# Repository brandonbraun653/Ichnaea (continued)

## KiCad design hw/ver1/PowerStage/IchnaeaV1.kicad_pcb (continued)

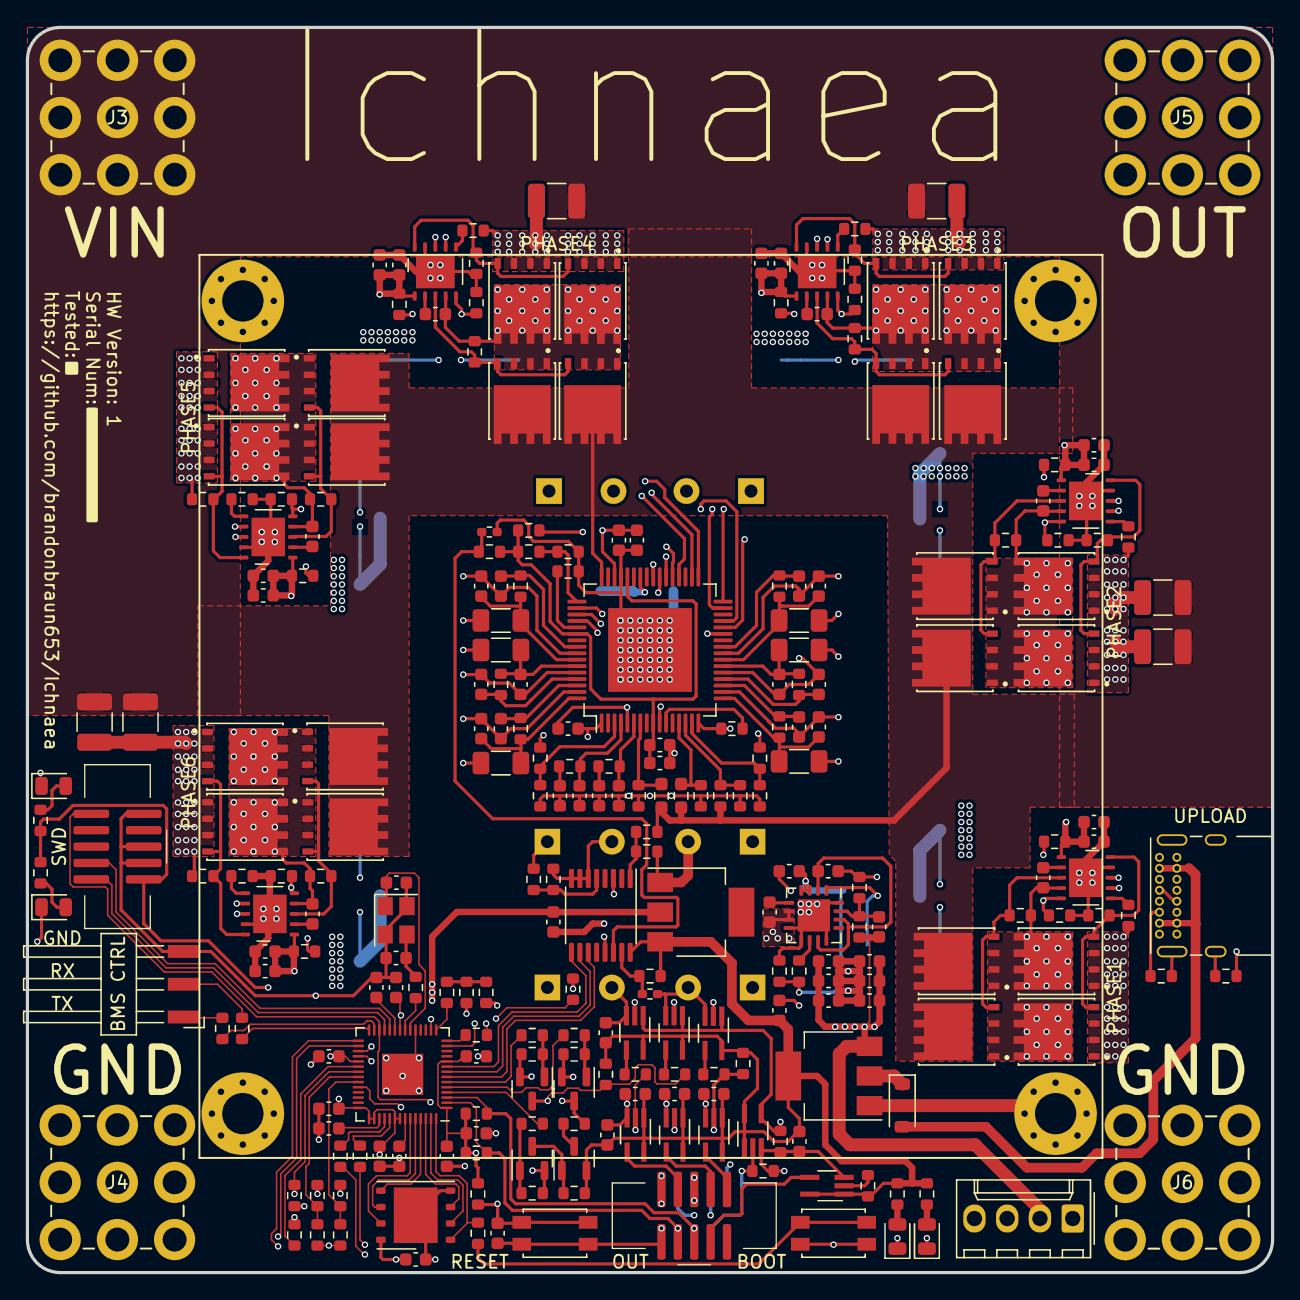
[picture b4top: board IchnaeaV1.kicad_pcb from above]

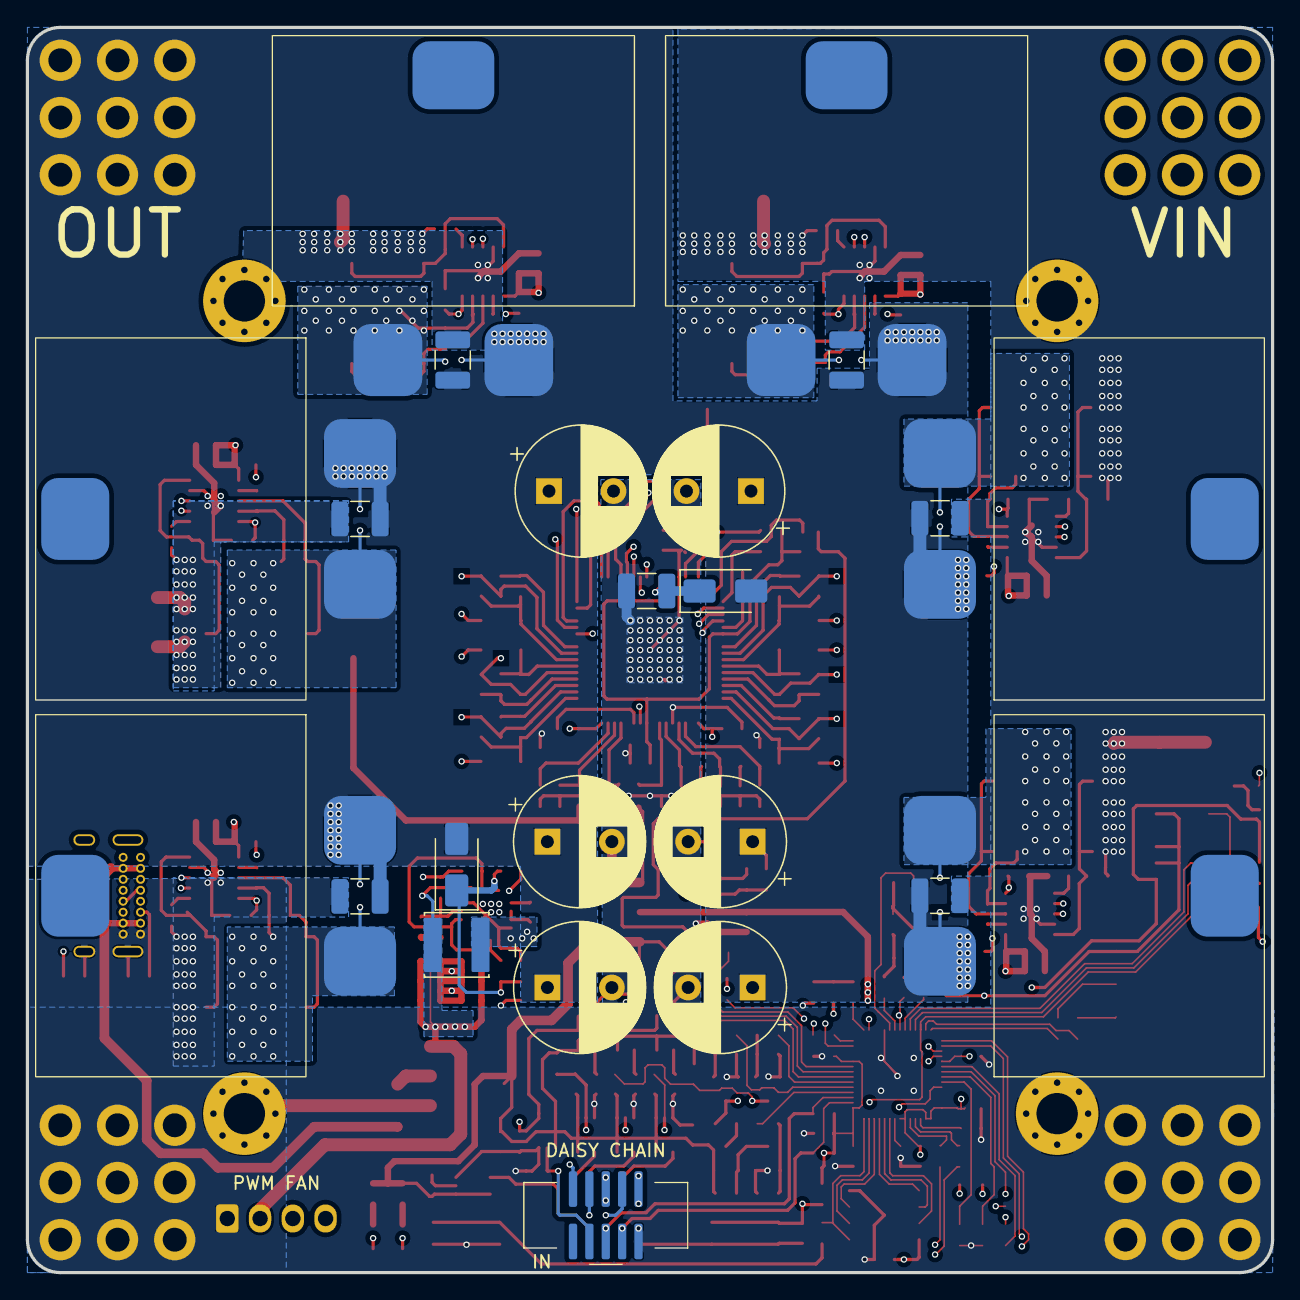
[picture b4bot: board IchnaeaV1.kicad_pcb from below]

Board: 4 copper layers, 96.5 x 96.5 mm, 283 parts (23 on the bottom side), 165 nets.

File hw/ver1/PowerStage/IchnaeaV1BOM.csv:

Reference,Value,Digikey,LCSC,Footprint,Datasheet,Qty,DNP
"R1,R55,R60,R65,R70,R75,R102,R103,R104,R110,R112",0,N/A,C21189,Resistor_SMD:R_0603_1608Metric,~,11,
"C71,C79",15pF,N/A,C1644,Capacitor_SMD:C_0603_1608Metric,~,2,
"C12,C13,C77",47pF,N/A,C1671,Capacitor_SMD:C_0603_1608Metric,~,3,
"C2,C4,C8,C10,C11,C14,C15,C29,C31,C35,C37,C41,C43,C47,C49,C53,C55,C60,C61,C65,C66,C67,C68,C70,C72,C82,C83,C84,C86,C87,C88,C90,C91,C92,C93",100nF,N/A,C14663,Capacitor_SMD:C_0603_1608Metric,~,35,
"C3,C5,C30,C32,C36,C38,C42,C44,C48,C50,C54,C56",470nF,N/A,C1623,Capacitor_SMD:C_0603_1608Metric,~,12,
"C1,C18,C21,C28,C34,C40,C46,C52,C78,C80,C81,C89",4.7uF,N/A,C19666,Capacitor_SMD:C_0603_1608Metric,~,12,
"L1,L2,L3,L4,L5,L6",4.7uH,PQ2614BLA-3R3K-ND,N/A,Inductors:Bournes_L_PQ2614BLA,~,6,
"C7,C9,C69,C73,C74,C75,C76",10uF,N/A,C96446,Capacitor_SMD:C_0603_1608Metric,~,7,
L7,22uH,240-2706-1-ND,N/A,Inductors:TYS5020220M,~,1,
"C22,C25,C26,C27,C62,C63",220uF,1189-3789-1-ND,N/A,Capacitor_THT:CP_Radial_D10.0mm_P5.00mm,~,6,
"R24,R26",22,N/A,C23345,Resistor_SMD:R_0603_1608Metric,~,2,
"R11,R19,R49,R50",100,N/A,C22775,Resistor_SMD:R_0603_1608Metric,~,4,
"R9,R10,R131,R132",510,N/A,C23193,Resistor_SMD:R_0603_1608Metric,~,4,
"R6,R32,R107,R117,R118,R119,R121,R128",1k,N/A,C21190,Resistor_SMD:R_0603_1608Metric,~,8,
"R8,R120,R129",2k,N/A,C22975,Resistor_SMD:R_0603_1608Metric,~,3,
R31,3k,N/A,C4211,Resistor_SMD:R_0603_1608Metric,~,1,
"R93,R94",4.7k,N/A,C23162,Resistor_SMD:R_0603_1608Metric,~,2,
"R108,R109",5.1k,N/A,C23186,Resistor_SMD:R_0603_1608Metric,~,2,
"R5,R59,R64,R69,R74,R79",6.2k,N/A,C4260,Resistor_SMD:R_0603_1608Metric,~,6,
R98,7.5k,N/A,C23234,Resistor_SMD:R_0603_1608Metric,~,1,
"R2,R3,R12,R13,R16,R21,R23,R28,R30,R33,R35,R44,R45,R46,R48,R51,R52,R53,R54,R56,R57,R61,R62,R66,R67,R71,R72,R76,R77,R80,R81,R82,R83,R84,R85,R86,R87,R88,R89,R90,R91,R92,R95,R96,R97",10k,N/A,C25804,Resistor_SMD:R_0603_1608Metric,~,45,
"TH1,TH2",10k-NTC,445-2550-1-ND,N/A,Resistor_SMD:R_0402_1005Metric_Pad0.72x0.64mm_HandSolder,~,2,
"R18,R39",15k,N/A,C22809,Resistor_SMD:R_0603_1608Metric,~,2,
R7,22k,N/A,C31850,Resistor_SMD:R_0603_1608Metric,~,1,
R15,27k,N/A,C22967,Resistor_SMD:R_0603_1608Metric,~,1,
R36,30k,N/A,C22984,Resistor_SMD:R_0603_1608Metric,~,1,
"R27,R100",68k,N/A,C23231,Resistor_SMD:R_0603_1608Metric,~,2,
R29,100k,N/A,C25803,Resistor_SMD:R_0603_1608Metric,~,1,
R42,120k,N/A,C25808,Resistor_SMD:R_0603_1608Metric,~,1,
"R14,R17,R22,R43",470k,N/A,C23178,Resistor_SMD:R_0603_1608Metric,~,4,
R99,510k,N/A,C23192,Resistor_SMD:R_0603_1608Metric,~,1,
"R41,R47",787k,P787KHCT-ND,N/A,Resistor_SMD:R_0603_1608Metric_Pad0.98x0.95mm_HandSolder,~,2,
Y1,12MHz,XC2613CT-ND,N/A,Crystal:Crystal_SMD_3225-4Pin_3.2x2.5mm,~,1,
"C6,C33,C39,C45,C51,C57,C64",10uF-75V,445-CGA6P1X7R1N106M250ACCT-ND,,Capacitor_SMD:C_1210_3225Metric_Pad1.33x2.70mm_HandSolder,~,7,
"C19,C20,C23,C24,C58,C59",10uF-100V,490-16266-1-ND,,Capacitor_SMD:C_1210_3225Metric_Pad1.33x2.70mm_HandSolder,~,6,
"R4,R58,R63,R68,R73,R78",6.2k-0.25w,311-6.20KFRCT-ND,N/A,Resistor_SMD:R_1206_3216Metric_Pad1.30x1.75mm_HandSolder,~,6,
"U11,U12,U13,U14,U15,U16,U17,U18",74AHC1G126,74AHCT1G126SE-7DICT-ND,N/A,Package_TO_SOT_SMD:SOT-353_SC-70-5_Handsoldering,http://www.ti.com/lit/sg/scyt129e/scyt129e.pdf,8,
U2,74HC4051PW,1727-3064-1-ND,N/A,Package_SO:TSSOP-16_4.4x5mm_P0.65mm,http://www.ti.com/lit/ds/symlink/cd74hc4051.pdf,1,
U19,AP66200FVBW-13,31-AP66200FVBW-13CT-ND,N/A,Package_DFN_QFN:QFN-16-1EP_4x4mm_P0.65mm_EP2.5x2.5mm,https://www.diodes.com/assets/Datasheets/AP66200.pdf,1,
D4,B5819W,N/A,C8598,Diode_SMD:D_SOD-123,~,1,
J11,BMS_Serial,952-3232-ND,N/A,Connector_Harwin:Harwin_M20-89003xx_1x03_P2.54mm_Horizontal,~,1,
SW3,Boot,P11081SCT-ND,N/A,Button_Switch_SMD:SW_SPST_EVQP2,~,1,
Q5,BSS84,5272-BSS84CT-ND,N/A,Package_TO_SOT_SMD:SOT-23,http://assets.nexperia.com/documents/data-sheet/BSS84.pdf,1,
"Q3,Q4,Q6",BSS138,5272-BSS138CT-ND,N/A,Package_TO_SOT_SMD:SOT-23,https://www.onsemi.com/pub/Collateral/BSS138-D.PDF,3,
J1,DaisyChain-In,1175-1629-ND,N/A,Connectors:JTAG_2x05_P1_27mm_Shrouded_SMD,~,1,
J9,DaisyChain-Out,1175-1629-ND,N/A,Connectors:JTAG_2x05_P1_27mm_Shrouded_SMD,~,1,
J8,FanConnector,WM4330-ND,N/A,Connector_Molex:Molex_KK-254_AE-6410-04A_1x04_P2.54mm_Vertical,~,1,
"D2,D7",Green LED,N/A,C2297,LED_SMD:LED_0805_2012Metric,~,2,
"U1,U5,U6,U7,U8,U9",HIP2210,20-HIP2210FRTZ-TCT-ND,N/A,DFN:TDFN-10-1EP_4x4mm_P0.8mm_EP2.6x3mm,https://www.renesas.com/us/en/document/dst/hip2210-hip2211-d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,6,
U4,LM1117MP-3.3,N/A,C6186,Package_TO_SOT_SMD:SOT-223-3_TabPin2,http://www.ti.com/lit/ds/symlink/lm1117.pdf,1,
U21,LM1117MP-5.0,N/A,C6187,Package_TO_SOT_SMD:SOT-223-3_TabPin2,http://www.ti.com/lit/ds/symlink/lm1117.pdf,1,
U3,LTC7871,505-LTC7871ELWE#PBF-ND,C690288,Package_QFP:LQFP-64-1EP_10x10mm_P0.5mm_EP6.5x6.5mm,https://www.analog.com/media/en/technical-documentation/data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,1,
"Q1,Q2,Q7,Q8,Q9,Q10,Q11,Q12,Q13,Q14,Q15,Q16,Q17,Q18,Q19,Q20,Q21,Q22,Q23,Q24,Q25,Q26,Q27,Q28",MCAC80N10Y,353-MCAC80N10Y-TPCT-ND,N/A,Mosfets:TRANS_BSC076N06NS3-G,https://www.mccsemi.com/pdf/Products/MCAC80N10Y(DFN5060).pdf,24,
SW4,Reset,P11081SCT-ND,N/A,Button_Switch_SMD:SW_SPST_EVQP2,~,1,
U10,RP2040,2648-SC0914(13)CT-ND,C2040,Package_DFN_QFN:QFN-56-1EP_7x7mm_P0.4mm_EP3.2x3.2mm,https://datasheets.raspberrypi.com/rp2040/rp2040-datasheet.pdf,1,
"J3,J4,J5,J6",Screw_Terminal_01x09,732-74651195RCT-ND,N/A,Connectors:CONN_74651195R_WRE,~,4,
"D1,D3",SS210,N/A,C14996,Diode_SMD:D_SMA,~,2,
P1,USB_C_Plug_USB2.0,2073-USB4085-GF-ACT-ND,N/A,Connector_USB:USB_C_Receptacle_GCT_USB4085,https://www.usb.org/sites/default/files/documents/usb_type-c.zip,1,
U20,W25Q32JVZP,W25Q32JVZPIQ-ND,N/A,Package_SON:WSON-8-1EP_6x5mm_P1.27mm_EP3.4x4.3mm,http://www.winbond.com/resource-files/w25q32jv%20revg%200327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,1,
"D5,D6",Yellow LED,N/A,C2296,LED_SMD:LED_0805_2012Metric,~,2,
J2,~,1175-1629-ND,,Connectors:JTAG_2x05_P1_27mm_Shrouded_SMD,~,1,

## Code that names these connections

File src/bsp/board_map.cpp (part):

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      s_board_map.gpio[ GPIO_LTC_ADCSEL0 ].pin     = BSPV1::GPIO::PIN_OUT_ADC_SEL_0;
      s_board_map.gpio[ GPIO_LTC_ADCSEL1 ].pin     = BSPV1::GPIO::PIN_OUT_ADC_SEL_1;
      s_board_map.gpio[ GPIO_LTC_ADCSEL2 ].pin     = BSPV1::GPIO::PIN_OUT_ADC_SEL_2;
      s_board_map.gpio[ GPIO_LTC_CCM ].pin         = BSPV1::GPIO::PIN_OUT_LTC_CCM;
      s_board_map.gpio[ GPIO_LTC_DCM ].pin         = BSPV1::GPIO::PIN_OUT_LTC_DCM;
      s_board_map.gpio[ GPIO_LTC_RUN ].pin         = BSPV1::GPIO::PIN_IO_LTC_RUN;
      s_board_map.gpio[ GPIO_SPI_CS_LTC ].pin      = BSPV1::SPI::PIN_CS_0;
      s_board_map.pwm[ PWM_FAN_CONTROL ].pin       = BSPV1::PWM::PIN_OUT_FAN_CTL;
      s_board_map.pwm[ PWM_FAN_SENSE ].pin         = BSPV1::PWM::PIN_IN_FAN_SENSE;
      s_board_map.pwm[ PWM_LED_STATUS_0 ].pin      = BSPV1::GPIO::PIN_OUT_LED_STATUS_0;
      s_board_map.pwm[ PWM_LED_STATUS_1 ].pin      = BSPV1::GPIO::PIN_OUT_LED_STATUS_1;
      s_board_map.pwm[ PWM_LED_STATUS_2 ].pin      = BSPV1::GPIO::PIN_OUT_LED_STATUS_2;
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      s_board_map.ltc_num_phases                   = 6;
      s_board_map.ltc_setcur_rfb                   = 22'000.0f;
      s_board_map.adc[ ADC_MUTLIPLEXED_SENSE ].pin = BSPV2::ADC::PIN_MULTIPLEX;
      s_board_map.adc[ ADC_BOARD_REV ].pin         = BSPV2::ADC::PIN_BOARD_REV;
      s_board_map.adc[ ADC_IMON_BATT ].pin         = BSPV2::ADC::PIN_IMON_BATT;
      s_board_map.adc[ ADC_IMON_FLTR ].pin         = BSPV2::ADC::PIN_IMON_FLTR;
      s_board_map.gpio[ GPIO_LTC_ADCSEL0 ].pin     = BSPV2::GPIO::PIN_OUT_ADC_SEL_0;
      s_board_map.gpio[ GPIO_LTC_ADCSEL1 ].pin     = BSPV2::GPIO::PIN_OUT_ADC_SEL_1;
      s_board_map.gpio[ GPIO_LTC_ADCSEL2 ].pin     = BSPV2::GPIO::PIN_OUT_ADC_SEL_2;
      s_board_map.gpio[ GPIO_LTC_CCM ].pin         = BSPV2::GPIO::PIN_OUT_LTC_CCM;
      s_board_map.gpio[ GPIO_LTC_DCM ].pin         = BSPV2::GPIO::PIN_OUT_LTC_DCM;
      s_board_map.gpio[ GPIO_LTC_RUN ].pin         = BSPV2::GPIO::PIN_OUT_LTC_RUN;
      s_board_map.gpio[ GPIO_LTC_PWMEN ].pin       = BSPV2::GPIO::PIN_OUT_LTC_PWMEN;
      s_board_map.gpio[ GPIO_SPI_CS_LTC ].pin      = BSPV2::SPI::PIN_LTC_CS_0;
      s_board_map.gpio[ GPIO_SPI_CS_NOR ].pin      = BSPV2::SPI::PIN_NOR_CS_0;
      s_board_map.pwm[ PWM_FAN_CONTROL ].pin       = BSPV2::PWM::PIN_OUT_FAN_CTL;
      s_board_map.pwm[ PWM_FAN_SENSE ].pin         = BSPV2::PWM::PIN_IN_FAN_SENSE;
      s_board_map.pwm[ PWM_LED_STATUS_0 ].pin      = BSPV2::PWM::PIN_OUT_LED_STATUS_0;
      s_board_map.pwm[ PWM_LED_STATUS_1 ].pin      = BSPV2::PWM::PIN_OUT_LED_STATUS_1;
      s_board_map.pwm[ PWM_LED_STATUS_2 ].pin      = BSPV2::PWM::PIN_OUT_LED_STATUS_2;
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
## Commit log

2024-02-13 Start adding initial v1 design
2024-02-14 Add personal kicad library
2024-02-15 Add virtual environment. Layout some schematic ideas. Add design doc for LTC7871.
2024-04-24 Pull up espressif lib to v3.0.0 for KiCAD 8 support
2024-04-24 Save off some design steps from lunch
2024-04-26 Start working through inductor calculations
2024-04-30 Sync work from this past weekend
2024-05-01 Save the day's effort
2024-05-02 Flesh out some more of the power design
2024-05-02 Save lunch work
2024-05-03 Save this morning's effort
2024-05-03 Split controller from the power stage. Get a better high level system flow.
2024-05-04 Sync wip
2024-05-05 Sync wip for parametric analyzer
2024-05-05 Very rough cut of a parameterized design validator
2024-05-05 Save off work from before lunch.
2024-05-05 Do some parameterized designs and SPICE simulations with the LTC7871.
2024-05-06 Save lunchtime work
2024-05-08 Add component part numbers for ordering. Resolve footprints.
2024-05-10 Sync some start to the PCB design
2024-05-13 Mess with the buck design. Tear out previous approach.
2024-05-14 Sync lunch work
2024-05-15 Sync work to laptop
2024-05-15 Lunch effort. Add models for screw terminals. Work on power distribution planes.
2024-05-16 More power plane work. Double mosfets.
2024-05-17 Improve power routing
2024-05-17 Sync effort from before work
2024-05-19 Improve power layout. Finish most of the initial routing for the LTC7871
2024-05-19 Pull up submodules
2024-05-19 Sync morning work to laptop
2024-05-20 Add low voltage switching supply
2024-05-20 Sync this morning's effort
2024-05-21 Sync tonight's effort
2024-05-22 Start optimizing some of the layout to make room for control circuitry
2024-05-24 Improve low voltage power layout
2024-05-26 Sync work
2024-05-27 Sync yesterday's effort
2024-05-27 Finish the initial route before DRC
2024-05-27 Resolve DRC errors
2024-05-29 Sync some work from this morning
2024-05-30 Add hardware board version 1.0
2024-06-08 Add a basic blinky. Trying to figure out debug attachment and CPU wake.
2024-06-08 Figured out how to program the board
2024-06-09 Sync back to main pc
2024-06-10 Start adding safety net for board map detection. Add beginnings of documentation and test framework.
2024-06-18 Started figuring out how to mock the PicoSDK for driver testing. Pretty neat.
2024-06-18 Fix a build issue from an accidental file reversion.
2024-06-18 Fix some issues with cmake targets. Realized I was building code multiple times in static libraries.
2024-06-19 Sync some board changes
2024-06-19 Clean up some of the build files
2024-06-19 Start adding system execution infrastructure
2024-06-20 Lunch work. Get the LED interface mostly working.
2024-06-21 Added PWM control to on-board LEDs. Nice POST sequence for them too.
2024-06-22 Start work on the UART and ADC interfaces
2024-06-22 Write a minimal ADC driver. Start on the SPI access to the LTC7871.
2024-06-23 Found a bunch of HW errors regarding LTC control.
2024-06-23 Resolve communication issues with the LTC7871. Need some HW modifications for V2.
2024-06-23 Jot down some notes for boot configuration resolution
2024-06-23 Finish out the LTC post checkout
2024-06-26 Start working on the plumbing for uart output
2024-06-27 Add more plumbing. Need a bunch of integration effort for the mbedutils library now.
2024-06-27 Add stubs for logging/assert module integration over lunch.
2024-06-28 Fill in some of the stubs for mbedutils
2024-06-29 Sync work from lunch
2024-06-29 Add some NotesForV2
2024-06-29 Refactor board map access to be a bit more flexible
2024-06-29 Update stubs for the serial interface
2024-06-29 Pull up mbedutils
2024-07-01 Testing out the serial driver. Ichnaea is now a rap god.
2024-07-02 Trying out some ideas with dma reception
2024-07-03 Sync back to laptop
2024-07-03 Working DMA transaction with echo
2024-07-04 Validate simple echo from serial interface
2024-07-05 Work on ADC bringup
2024-07-05 Fix an issue with ADC measurements
2024-07-05 Add LTC7871 fault status analysis to POST
2024-07-07 Experiment with the voltage control loop
2024-07-08 Sketch out fan driver/sense support. Start trying to figure out the SYNC pin support.
2024-07-08 Clean up fan controller. Add SYNC pin control.
2024-07-09 Add LTC SYNC support.
2024-07-09 Add note on smps for gate drive.
2024-07-11 Sync submodules
2024-07-11 Add a few more notes
2024-07-11 Sync this morning's work
2024-07-12 Sync back to main pc.
2024-07-14 Start testing out first cut of RPC server
2024-07-17 Start trying to ping the board through rpc
2024-07-20 Sync
2024-07-20 Validate basic RPC ping service. Start integrating FreeRTOS.
2024-07-22 Start integrating some more of threading changes
2024-07-24 Pull up submodule. Trying to get multi-core FreeRTOS working...
2024-07-24 Figure out some things with SMP debugging in FreeRTOS
2024-07-26 More improvements. sync back to main pc
2024-07-27 Remote message logging working. Start adding proto integration for system identification and control.
2024-07-27 Start adding the Ichnaea python package as a consumable driver
2024-07-29 Start adding services for controlling/inspecting the LTC7871.
2024-07-29 Start adding interfaces to program LTC7871 registers via RPC
2024-07-30 Add engage/disengage methods to LTC control
2024-07-31 Try switching over to FreeRTOS mutexes and semaphores
2024-07-31 Start testing out voltage sweeps for controllable LTC7871 ranges
2024-08-01 Fix serial driver issue with attempts to flood the rx buffers.
2024-08-02 Pull up submodules. Add test for commanding voltages.
2024-08-03 Commanded sweep of output voltage. Still getting some excessive noise/current draw.
2024-08-04 Start work on V2 of the power stage
2024-08-05 Trying to optimize the high power loop area
2024-08-06 Trying to further compress power loop area
2024-08-07 Not quite happy with the power stage just yet.
2024-08-09 Sync work to main PC
2024-08-10 More power stage layout
2024-08-11 Partially work through the V1 notes. Start adding some of the control stage circuitry.
2024-08-12 Add pin mapping doc
2024-08-13 Partial pin mapping. ESD protection on signals that exit the board.
2024-08-13 More routing considerations for logic stage
2024-08-16 Sync to main pc
2024-08-17 Finish the initial rough route/placement
2024-08-18 Finish routing V2
2024-08-19 Test production outputs for V2
2024-08-20 Resolve missing components from local stock. Order V2.
2024-08-20 Add driver support for V1 of the board. Revision HW to v2.0.
2024-09-01 Start working on V2 software support
2024-09-01 Sync schematic updates
2024-09-01 Move pico-sdk to v1.5.1
2024-09-02 Add support for new GPIO/LED mapping. Partial ADC support.
2024-09-02 System is booting, but I can't seem to talk over UART yet.
2024-09-04 Working debug port. Fix ADC voltage monitor calculations.
2024-09-04 Fix up environment to use python 3.12
2024-09-05 Fix issue with multi-port serial initialization
2024-10-13 Enhance LTC7871 control logic and update documentation
    - Added functions to set RUN and PWMEN pins for better power management.
    - Increased timeout for communication in ichnaea_client.py.
    - Updated assembly notes and circuit notes in NotesForV3.md.
    - Added new directory mapping for flashdb in vcs.xml.
    - Updated submodule references for mbedutils and pico-mock.
    - Adjusted test configuration for V2 hardware.
2024-10-13 Add new mbedutils submodules and update CMake configuration
2024-10-13 Refactor test structure: remove main_test_entry.cpp and integrate test execution in test_board_map.cpp
2024-10-13 Remove unused color customizations from workspace configuration
2024-10-13 Remove Ichnaea workspace configuration file
2024-10-13 Update mock scripts. Fix testing support.
2024-10-14 Add NOR and system configuration modules; update submodules and tests
2024-10-16 Refactor NOR interface: rename initialize to init, add read, write, and erase functions; update flash device descriptor
2024-10-16 Update submodule mbedutils_pico to latest commit
2024-10-16 Add mbedutils_test submodule to .gitmodules
2024-10-16 Update submodules mbedutils and mbedutils_pico to latest commits
2024-10-19 Update submodules mbedutils, mbedutils_pico, and mbedutils_freertos; add flashdb integration and update board map
2024-10-21 Update submodules mbedutils and mbedutils_pico; add PDI interface implementation and related build configurations
2024-10-21 Disable Wextra compiler warning in CMakeLists.txt
2024-10-22 Add linker script and update development environment configurations
2024-10-23 Update development environment: modify devcontainer and Dockerfile, add extensions, and adjust compiler settings
2024-10-23 Remove FlashDB submodule and update mbedutils submodule reference; enhance NOR write function with integrity check and add debug logging
2024-10-23 Update NOR write function with integrity check and debug logging; adjust app_stats for boot count sync; modify task storage size; enable natural format for Cortex-Debug
2024-10-24 Update app_stats and system_db for boot count synchronization; refine NVM KVDB configuration and clean up unused code
2025-01-19 Add support for HW v2 of the board + system testing infrastructure
2025-01-20 More experimentation with serialization issue
2025-01-21 Partially fix HW logging tests
2025-01-22 Try getting tests to run on a task
2025-01-22 Figure out how to get pytest running correctly from the terminal. Add task to run all simulator tests on demand.
2025-01-22 Import bug fixes. Prep for initial load testing.
2025-01-23 Start working power stage control logic. Add dedicated thread for delayed IO operations.
2025-01-25 Work on more robust enable procedure
2025-01-25 Confirm boot issue fix for simulators
2025-01-25 Validate power-on control flow
2025-01-26 Fix a configuration issue that led to bad Vout programming on the LTC7871
2025-01-26 Improve error reporting on system faults
2025-01-28 Make some notes for V3.
2025-02-01 Start working on v3
2025-02-02 Experiment with a new power stage layout
2025-02-06 Tested the V2 board at 1.15kW load. Made some notes on system design for V3.
2025-02-08 I might've made a critical error
2025-02-08 Swiftly correct the design issue.
2025-02-09 Cost optimize power terminal connections
2025-02-09 Complete an improvement in notes
2025-02-15 Improve more of the power stage layout
2025-02-16 Start rework of power stage layout to shorten inductive path and increase current handling
2025-02-18 Greatly improve power routing. Add gate control drive.
2025-02-22 Begin routing switching controller signals
2025-02-23 Route power control signals. Upgrade to KiCad v9.0.0.
2025-03-02 Split the design into four major components. Start working on system architecture.
2025-03-02 Redo some charger routing. Improve design for interconnect
2025-03-03 Initial schematic for InterConnectV1
2025-03-08 Nearly final charger schematic, updated with RS485 interconnect.
2025-03-08 Update some notes
2025-03-12 Sync board changes from before work started
